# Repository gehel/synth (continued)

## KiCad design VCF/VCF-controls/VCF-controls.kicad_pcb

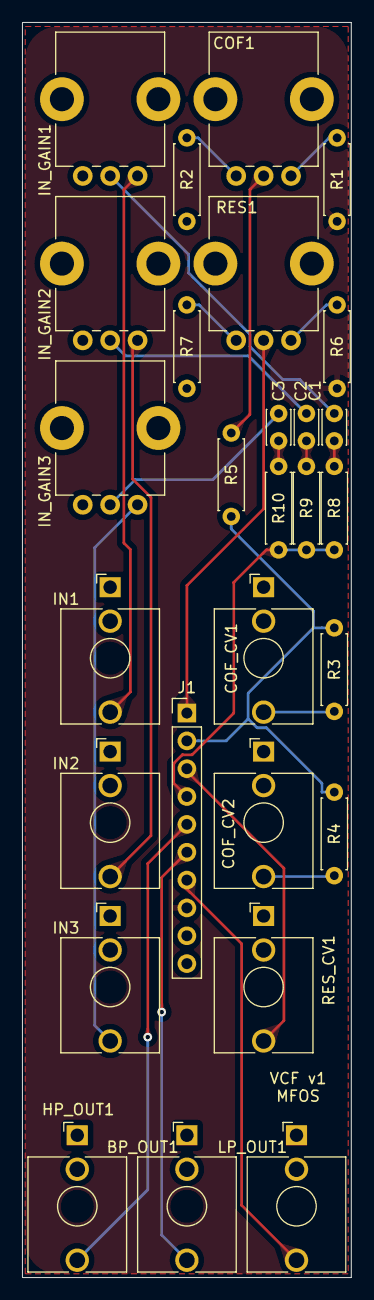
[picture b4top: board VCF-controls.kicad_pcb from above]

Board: 4 copper layers, 30.0 x 114.5 mm, 28 parts (0 on the bottom side), 26 nets.

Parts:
BP_OUT1: AudioJack2; Jack_3.5mm_QingPu_WQP-PJ398SM_Vertical_CircularHoles
C1, C2, C3: 100nF; C_Disc_D3.0mm_W2.0mm_P2.50mm
COF1: R_Potentiometer_MountingPin; Potentiometer_Bourns_PTV09A-1_Single_Vertical
COF_CV1, COF_CV2: AudioJack2; Jack_3.5mm_QingPu_WQP-PJ398SM_Vertical_CircularHoles
HP_OUT1: AudioJack2; Jack_3.5mm_QingPu_WQP-PJ398SM_Vertical_CircularHoles
IN1, IN2, IN3: AudioJack2; Jack_3.5mm_QingPu_WQP-PJ398SM_Vertical_CircularHoles
IN_GAIN1, IN_GAIN2, IN_GAIN3: R_Potentiometer_MountingPin; Potentiometer_Bourns_PTV09A-1_Single_Vertical
J1: Conn_01x10; PinHeader_1x10_P2.54mm_Vertical
LP_OUT1: AudioJack2; Jack_3.5mm_QingPu_WQP-PJ398SM_Vertical_CircularHoles
R1, R2: 33K; R_Axial_DIN0207_L6.3mm_D2.5mm_P7.62mm_Horizontal
R3, R4, R5: 100K; R_Axial_DIN0207_L6.3mm_D2.5mm_P7.62mm_Horizontal
R6, R7: 49.9K; R_Axial_DIN0207_L6.3mm_D2.5mm_P7.62mm_Horizontal
R8, R9, R10: 1M; R_Axial_DIN0207_L6.3mm_D2.5mm_P7.62mm_Horizontal
RES1: R_Potentiometer_MountingPin; Potentiometer_Bourns_PTV09A-1_Single_Vertical
RES_CV1: AudioJack2; Jack_3.5mm_QingPu_WQP-PJ398SM_Vertical_CircularHoles

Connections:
+12V: J1.8, R1.1, R6.2
-12V: J1.9, R2.2, R7.1
AIN: J1.4, R8.2, R9.2, R10.2
BP: BP_OUT1.T, J1.6
CV/CO: J1.2, R3.2, R4.2, R5.2
GND: BP_OUT1.S, COF1.MP (MountPin), COF_CV1.S, COF_CV2.S, HP_OUT1.S, IN1.S, IN2.S, IN3.S, IN_GAIN1.3, IN_GAIN1.MP (MountPin), IN_GAIN2.3, IN_GAIN2.MP (MountPin), IN_GAIN3.3, IN_GAIN3.MP (MountPin), J1.10, LP_OUT1.S, RES1.MP (MountPin), RES_CV1.S
HP: HP_OUT1.T, J1.5
LP: J1.7, LP_OUT1.T
unnamed: C1.1, IN_GAIN1.2
unnamed: C1.2, R8.1
unnamed: C2.1, IN_GAIN2.2
unnamed: C2.2, R9.1
unnamed: C3.1, IN_GAIN3.2
unnamed: C3.2, R10.1
unnamed: COF1.1, R1.2
unnamed: COF1.2, R5.1
unnamed: COF1.3, R2.1
unnamed: COF_CV1.T, R3.1
unnamed: COF_CV2.T, R4.1
unnamed: IN1.T, IN_GAIN1.1
unnamed: IN2.T, IN_GAIN2.1
unnamed: IN3.T, IN_GAIN3.1
unnamed: R6.1, RES1.1
unnamed: R7.2, RES1.3
RES: J1.1, RES1.2
XRES: J1.3, RES_CV1.T

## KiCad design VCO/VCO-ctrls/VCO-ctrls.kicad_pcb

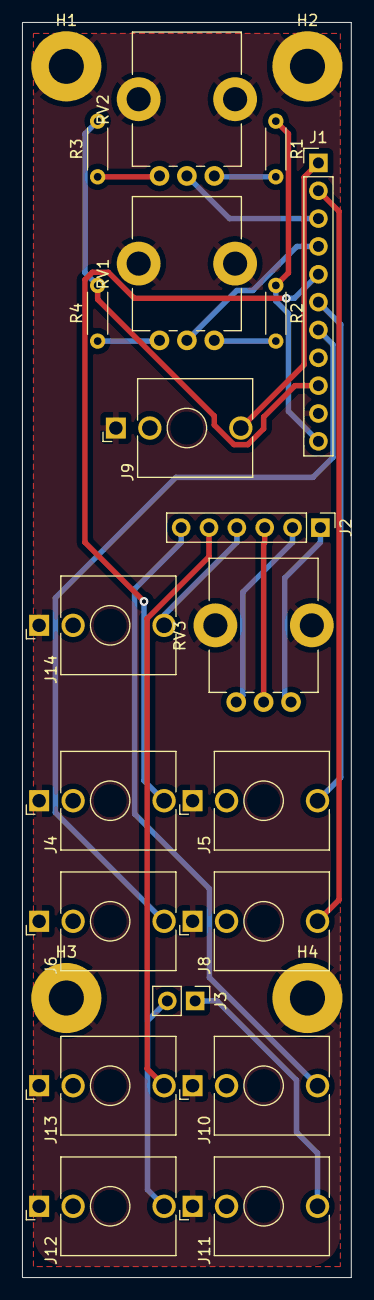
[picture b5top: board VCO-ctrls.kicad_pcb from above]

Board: 2 copper layers, 30.0 x 114.5 mm, 24 parts (0 on the bottom side), 22 nets.

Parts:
H1, H2, H3, H4: MountingHole_Pad; MountingHole_3.2mm_M3_Pad
J1: Conn_01x11; PinHeader_1x11_P2.54mm_Vertical
J2: Conn_01x06; PinHeader_1x06_P2.54mm_Vertical
J3: Conn_01x02; PinHeader_1x02_P2.54mm_Vertical
J4, J5, J6, J8, J9, J10, J11, J12, J13, J14: AudioJack2; Jack_3.5mm_QingPu_WQP-PJ398SM_Vertical_CircularHoles
R1, R3: 200K; R_Axial_DIN0204_L3.6mm_D1.6mm_P5.08mm_Horizontal
R2: 10K; R_Axial_DIN0204_L3.6mm_D1.6mm_P5.08mm_Horizontal
R4: 47K; R_Axial_DIN0204_L3.6mm_D1.6mm_P5.08mm_Horizontal
RV1, RV2, RV3: 100K; Potentiometer_Bourns_PTV09A-1_Single_Vertical

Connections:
+12V: J1.9, R3.2, R4.2
-12V: J1.11, R1.1, R2.1
CV1: J1.5, J4.T
CV2: J1.6, J5.T
CV3: J1.7, J6.T
GND: H1.1, H2.1, H3.1, H4.1, J1.10, J4.S, J5.S, J6.S, J8.S, J9.S, J10.S, J11.S, J12.S, J13.S, J14.S
LIN: J1.2, J8.T
PWM: J2.4, J14.T
R2P1: R2.2, RV1.1
R2P2: J1.4, RV1.2
R2P3: R4.1, RV1.3
R3P1: R1.2, RV2.1
R3P2: J1.3, RV2.2
R3P3: R3.1, RV2.3
R39P1: J2.1, RV3.1
R39P2: J2.3, RV3.2
R39P3: J2.2, RV3.3
RMP: J3.2, J12.T
SIN: J2.6, J10.T
SQR: J2.5, J13.T
SYNC: J1.1, J9.T
TRI: J3.1, J11.T
